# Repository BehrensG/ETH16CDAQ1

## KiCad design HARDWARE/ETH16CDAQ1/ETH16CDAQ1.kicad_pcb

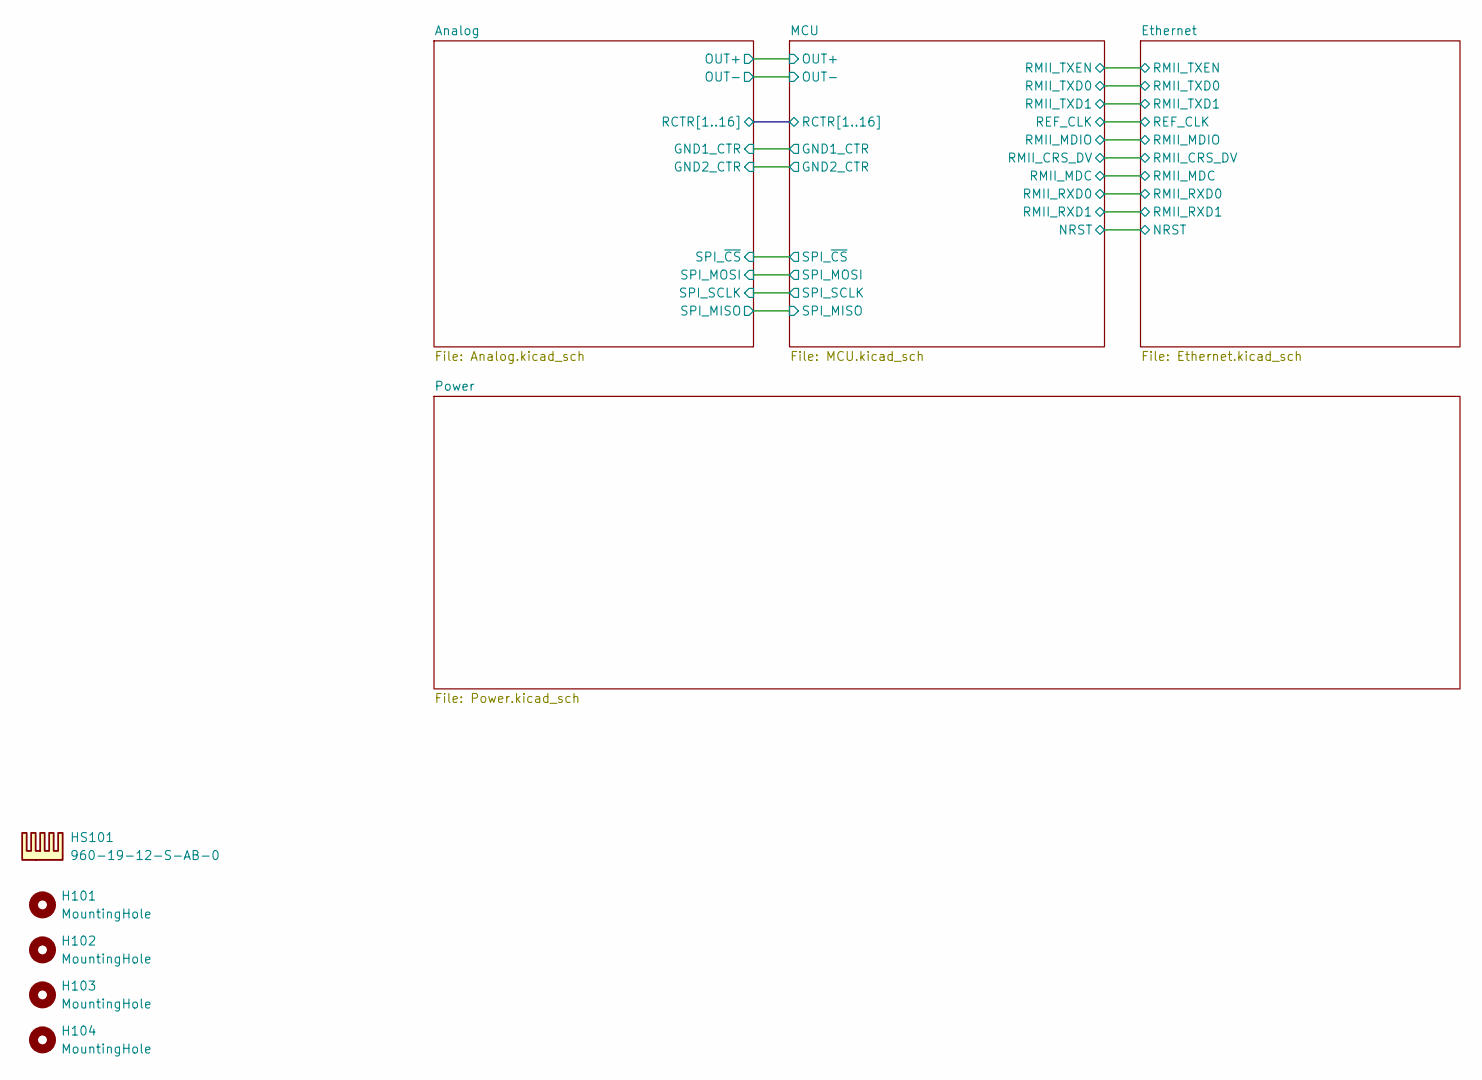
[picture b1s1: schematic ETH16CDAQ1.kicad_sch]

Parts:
H101, H102: MountingHole; MountingHole_3.2mm_M3_DIN965_Pad
H103, H104: MountingHole; MountingHole_2.2mm_M2_DIN965
HS101: 960-19-12-S-AB-0

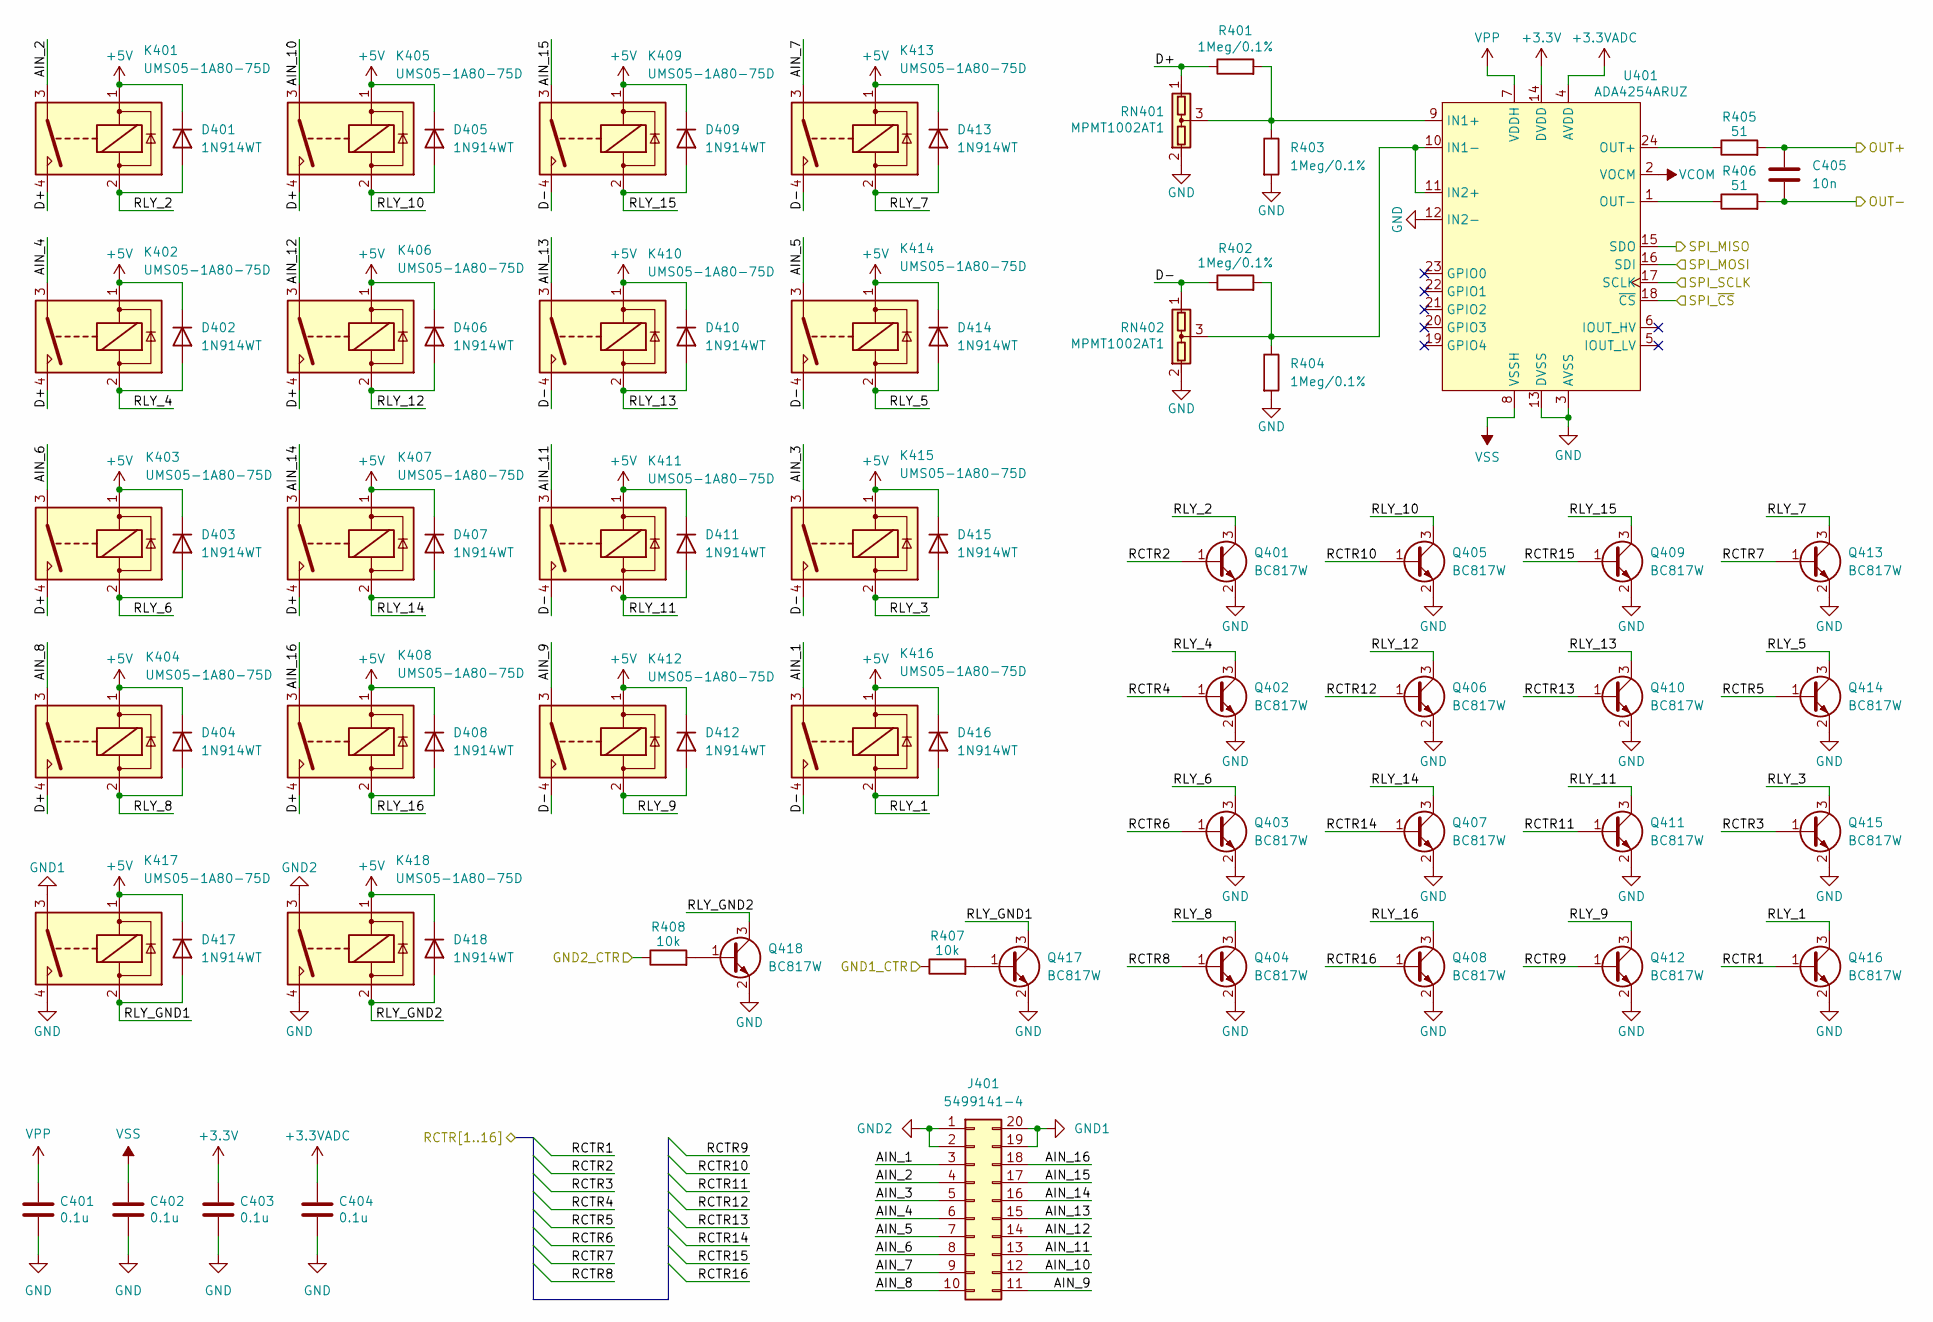
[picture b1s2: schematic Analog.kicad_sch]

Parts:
C401, C402, C403, C404: 0.1u; C_0603_1608Metric_Pad1.08x0.95mm_HandSolder
C405: 10n; C_0603_1608Metric_Pad1.08x0.95mm_HandSolder
D401, D402, D403, D404, D405, D406, D407, D408, D409, D410, D411, D412, D413, D414, D415, D416, D417, D418: 1N914WT; D_SOD-523
J401: 5499141-4; IDC-Header_2x10-1MP_P2.54mm_Latch_Horizontal
K401, K402, K403, K404, K405, K406, K407, K408, K409, K410, K411, K412, K413, K414, K415, K416, K417, K418: UMS05-1A80-75D; Relay_StandexMeder_UMS
Q401, Q402, Q403, Q404, Q405, Q406, Q407, Q408, Q409, Q410, Q411, Q412, Q413, Q414, Q415, Q416, Q417, Q418: BC817W; SOT-323_SC-70
R401, R402, R403, R404: 1Meg/0.1%; R_0805_2012Metric_Pad1.20x1.40mm_HandSolder
R405, R406: 51; R_0603_1608Metric_Pad0.98x0.95mm_HandSolder
R407, R408: 10k; R_0603_1608Metric_Pad0.98x0.95mm_HandSolder
RN401, RN402: MPMT1002AT1; SOT-23
U401: ADA4254ARUZ; TSSOP-24_4.4x7.8mm_P0.65mm

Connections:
+3.3V: C403.1, U401.14 (DVDD); also elsewhere on the board
+3.3VADC: C404.1, U401.4 (AVDD); also elsewhere on the board
+5V: D401.1 (K), D402.1 (K), D403.1 (K), D404.1 (K), D405.1 (K), D406.1 (K), D407.1 (K), D408.1 (K), D409.1 (K), D410.1 (K), D411.1 (K), D412.1 (K), D413.1 (K), D414.1 (K), D415.1 (K), D416.1 (K), D417.1 (K), D418.1 (K), K401.1, K402.1, K403.1, K404.1, K405.1, K406.1, K407.1, K408.1, K409.1, K410.1, K411.1, K412.1, K413.1, K414.1, K415.1, K416.1, K417.1, K418.1; also elsewhere on the board
/Analog/AIN_1: J401.3, K416.3
/Analog/AIN_2: J401.4, K401.3
/Analog/AIN_3: J401.5, K415.3
/Analog/AIN_4: J401.6, K402.3
/Analog/AIN_5: J401.7, K414.3
/Analog/AIN_6: J401.8, K403.3
/Analog/AIN_7: J401.9, K413.3
/Analog/AIN_8: J401.10, K404.3
/Analog/AIN_9: J401.11, K412.3
/Analog/AIN_10: J401.12, K405.3
/Analog/AIN_11: J401.13, K411.3
/Analog/AIN_12: J401.14, K406.3
/Analog/AIN_13: J401.15, K410.3
/Analog/AIN_14: J401.16, K407.3
/Analog/AIN_15: J401.17, K409.3
/Analog/AIN_16: J401.18, K408.3
/Analog/D+: K401.4, K402.4, K403.4, K404.4, K405.4, K406.4, K407.4, K408.4, R401.1, RN401.1
/Analog/D-: K409.4, K410.4, K411.4, K412.4, K413.4, K414.4, K415.4, K416.4, R402.1, RN402.1
/Analog/GND1_CTR: R407.1; also elsewhere on the board
/Analog/GND2_CTR: R408.1; also elsewhere on the board
/Analog/OUT+: C405.1, R405.2; also elsewhere on the board
/Analog/OUT-: C405.2, R406.2; also elsewhere on the board
/Analog/RCTR1: Q416.1 (B); also elsewhere on the board
/Analog/RCTR2: Q401.1 (B); also elsewhere on the board
/Analog/RCTR3: Q415.1 (B); also elsewhere on the board
/Analog/RCTR4: Q402.1 (B); also elsewhere on the board
/Analog/RCTR5: Q414.1 (B); also elsewhere on the board
/Analog/RCTR6: Q403.1 (B); also elsewhere on the board
/Analog/RCTR7: Q413.1 (B); also elsewhere on the board
/Analog/RCTR8: Q404.1 (B); also elsewhere on the board
/Analog/RCTR9: Q412.1 (B); also elsewhere on the board
/Analog/RCTR10: Q405.1 (B); also elsewhere on the board
/Analog/RCTR11: Q411.1 (B); also elsewhere on the board
/Analog/RCTR12: Q406.1 (B); also elsewhere on the board
/Analog/RCTR13: Q410.1 (B); also elsewhere on the board
/Analog/RCTR14: Q407.1 (B); also elsewhere on the board
/Analog/RCTR15: Q409.1 (B); also elsewhere on the board
/Analog/RCTR16: Q408.1 (B); also elsewhere on the board
/Analog/RLY_1: D416.2 (A), K416.2, Q416.3 (C)
/Analog/RLY_2: D401.2 (A), K401.2, Q401.3 (C)
/Analog/RLY_3: D415.2 (A), K415.2, Q415.3 (C)
/Analog/RLY_4: D402.2 (A), K402.2, Q402.3 (C)
/Analog/RLY_5: D414.2 (A), K414.2, Q414.3 (C)
/Analog/RLY_6: D403.2 (A), K403.2, Q403.3 (C)
/Analog/RLY_7: D413.2 (A), K413.2, Q413.3 (C)
/Analog/RLY_8: D404.2 (A), K404.2, Q404.3 (C)
/Analog/RLY_9: D412.2 (A), K412.2, Q412.3 (C)
/Analog/RLY_10: D405.2 (A), K405.2, Q405.3 (C)
/Analog/RLY_11: D411.2 (A), K411.2, Q411.3 (C)
/Analog/RLY_12: D406.2 (A), K406.2, Q406.3 (C)
/Analog/RLY_13: D410.2 (A), K410.2, Q410.3 (C)
/Analog/RLY_14: D407.2 (A), K407.2, Q407.3 (C)
/Analog/RLY_15: D409.2 (A), K409.2, Q409.3 (C)
/Analog/RLY_16: D408.2 (A), K408.2, Q408.3 (C)
/Analog/RLY_GND1: D417.2 (A), K417.2, Q417.3 (C)
/Analog/RLY_GND2: D418.2 (A), K418.2, Q418.3 (C)
/Analog/SPI_MISO: U401.15 (SDO); also elsewhere on the board
/Analog/SPI_MOSI: U401.16 (SDI); also elsewhere on the board
/Analog/SPI_SCLK: U401.17 (SCLK); also elsewhere on the board
/Analog/SPI_~CS: U401.18 (~CS); also elsewhere on the board
GND: C401.2, C402.2, C403.2, C404.2, K417.4, K418.4, Q401.2 (E), Q402.2 (E), Q403.2 (E), Q404.2 (E), Q405.2 (E), Q406.2 (E), Q407.2 (E), Q408.2 (E), Q409.2 (E), Q410.2 (E), Q411.2 (E), Q412.2 (E), Q413.2 (E), Q414.2 (E), Q415.2 (E), Q416.2 (E), Q417.2 (E), Q418.2 (E), R403.2, R404.2, RN401.2, RN402.2, U401.3 (AVSS), U401.12 (IN2-), U401.13 (DVSS); also elsewhere on the board
GND1: J401.19, J401.20, K417.3
GND2: J401.1, J401.2, K418.3
unnamed: Q417.1 (B), R407.2
unnamed: Q418.1 (B), R408.2
unnamed: R401.2, R403.1, RN401.3, U401.9 (IN1+)
unnamed: R402.2, R404.1, RN402.3, U401.10 (IN1-), U401.11 (IN2+)
unnamed: R405.1, U401.24 (OUT+)
unnamed: R406.1, U401.1 (OUT-)
VCOM: U401.2 (VOCM); also elsewhere on the board
VPP: C401.1, U401.7 (VDDH); also elsewhere on the board
VSS: C402.1, U401.8 (VSSH); also elsewhere on the board

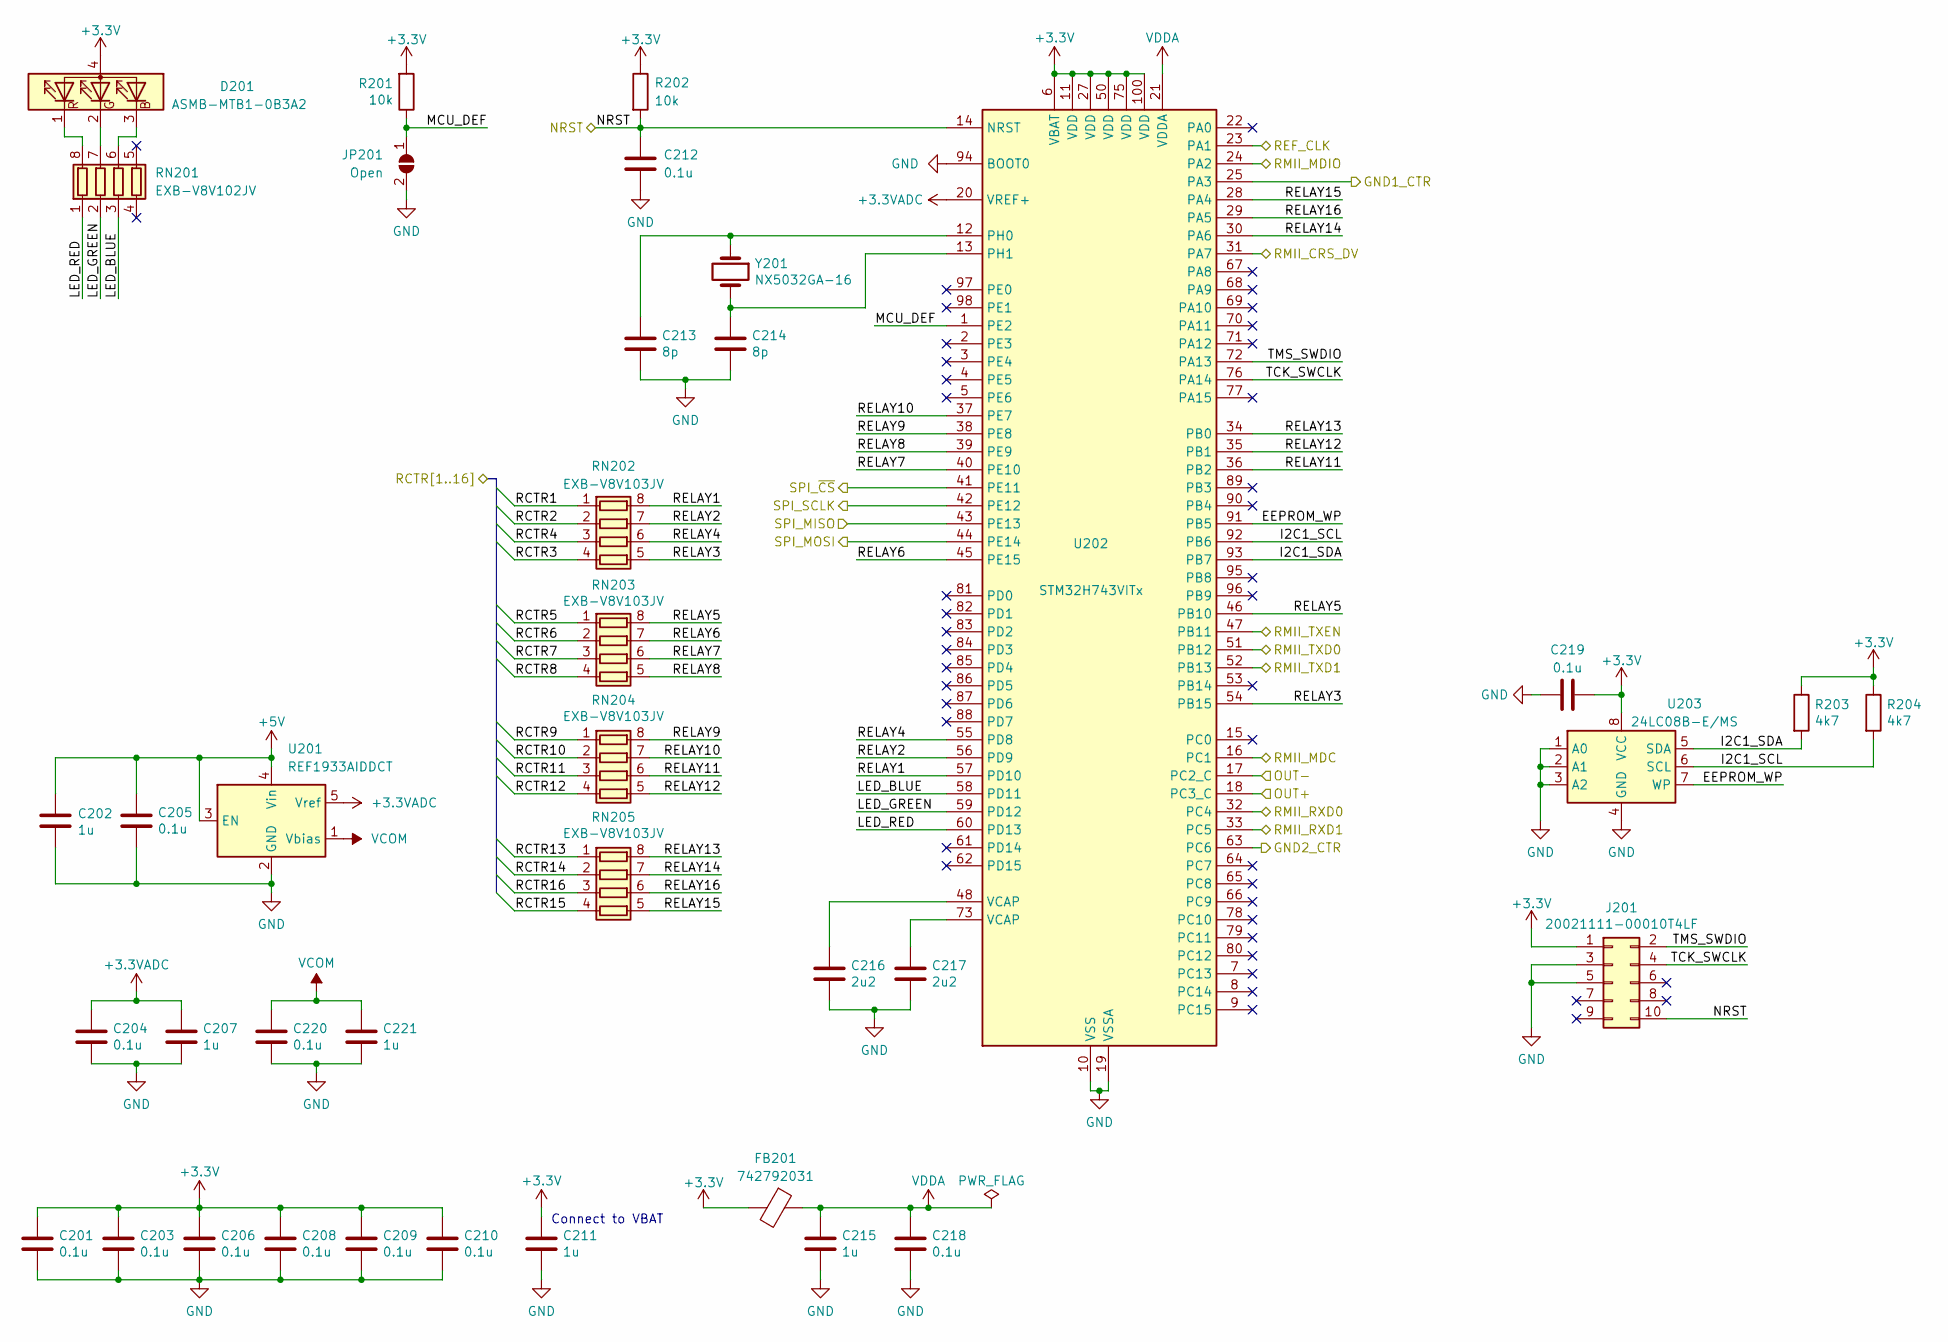
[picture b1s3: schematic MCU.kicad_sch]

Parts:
C201, C203, C204, C205, C206, C208, C209, C210, C212, C218, C219, C220: 0.1u; C_0603_1608Metric_Pad1.08x0.95mm_HandSolder
C202, C207, C211, C215, C221: 1u; C_0603_1608Metric_Pad1.08x0.95mm_HandSolder
C213, C214: 8p; C_0603_1608Metric_Pad1.08x0.95mm_HandSolder
C216, C217: 2u2; C_0603_1608Metric_Pad1.08x0.95mm_HandSolder
D201: ASMB-MTB1-0B3A2; LED_Avago_PLCC4_3.2x2.8mm_CW
FB201: 742792031; L_0805_2012Metric_Pad1.05x1.20mm_HandSolder
J201: 20021111-00010T4LF; PinHeader_2x05_P1.27mm_Vertical
JP201: Open; SolderJumper-2_P1.3mm_Open_Pad1.0x1.5mm
R201, R202: 10k; R_0603_1608Metric_Pad0.98x0.95mm_HandSolder
R203, R204: 4k7; R_0603_1608Metric_Pad0.98x0.95mm_HandSolder
RN201: EXB-V8V102JV; R_Array_Concave_4x0603
RN202, RN203, RN204, RN205: EXB-V8V103JV; R_Array_Concave_4x0603
U201: REF1933AIDDCT; TSOT-23-5
U202: STM32H743VITx; LQFP-100_14x14mm_P0.5mm
U203: 24LC08B-E/MS; MSOP-8_3x3mm_P0.65mm
Y201: NX5032GA-16; NX5032GA

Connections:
+3.3V: C201.1, C203.1, C206.1, C208.1, C209.1, C210.1, C211.1, C219.2, D201.4 (A), FB201.2, J201.1, R201.2, R202.1, R203.1, R204.1, U202.6 (VBAT), U202.11 (VDD), U202.27 (VDD), U202.50 (VDD), U202.75 (VDD), U202.100 (VDD), U203.8 (VCC); also elsewhere on the board
+3.3VADC: C204.1, C207.1, U201.5 (Vref), U202.20 (VREF+); also elsewhere on the board
+5V: C202.1, C205.1, U201.3 (EN), U201.4 (Vin); also elsewhere on the board
/Analog/GND1_CTR: U202.25 (PA3); also elsewhere on the board
/Analog/GND2_CTR: U202.63 (PC6); also elsewhere on the board
/Analog/OUT+: U202.18 (PC3_C); also elsewhere on the board
/Analog/OUT-: U202.17 (PC2_C); also elsewhere on the board
/Analog/RCTR1: RN202.1 (R1.1); also elsewhere on the board
/Analog/RCTR2: RN202.2 (R2.1); also elsewhere on the board
/Analog/RCTR3: RN202.4 (R4.1); also elsewhere on the board
/Analog/RCTR4: RN202.3 (R3.1); also elsewhere on the board
/Analog/RCTR5: RN203.1 (R1.1); also elsewhere on the board
/Analog/RCTR6: RN203.2 (R2.1); also elsewhere on the board
/Analog/RCTR7: RN203.3 (R3.1); also elsewhere on the board
/Analog/RCTR8: RN203.4 (R4.1); also elsewhere on the board
/Analog/RCTR9: RN204.1 (R1.1); also elsewhere on the board
/Analog/RCTR10: RN204.2 (R2.1); also elsewhere on the board
/Analog/RCTR11: RN204.3 (R3.1); also elsewhere on the board
/Analog/RCTR12: RN204.4 (R4.1); also elsewhere on the board
/Analog/RCTR13: RN205.1 (R1.1); also elsewhere on the board
/Analog/RCTR14: RN205.2 (R2.1); also elsewhere on the board
/Analog/RCTR15: RN205.4 (R4.1); also elsewhere on the board
/Analog/RCTR16: RN205.3 (R3.1); also elsewhere on the board
/Analog/SPI_MISO: U202.43 (PE13); also elsewhere on the board
/Analog/SPI_MOSI: U202.44 (PE14); also elsewhere on the board
/Analog/SPI_SCLK: U202.42 (PE12); also elsewhere on the board
/Analog/SPI_~CS: U202.41 (PE11); also elsewhere on the board
/Ethernet/REF_CLK: U202.23 (PA1); also elsewhere on the board
/Ethernet/RMII_CRS_DV: U202.31 (PA7); also elsewhere on the board
/Ethernet/RMII_MDC: U202.16 (PC1); also elsewhere on the board
/Ethernet/RMII_MDIO: U202.24 (PA2); also elsewhere on the board
/Ethernet/RMII_RXD0: U202.32 (PC4); also elsewhere on the board
/Ethernet/RMII_RXD1: U202.33 (PC5); also elsewhere on the board
/Ethernet/RMII_TXD0: U202.51 (PB12); also elsewhere on the board
/Ethernet/RMII_TXD1: U202.52 (PB13); also elsewhere on the board
/Ethernet/RMII_TXEN: U202.47 (PB11); also elsewhere on the board
/MCU/EEPROM_WP: U202.91 (PB5), U203.7 (WP)
/MCU/I2C1_SCL: R204.2, U202.92 (PB6), U203.6 (SCL)
/MCU/I2C1_SDA: R203.2, U202.93 (PB7), U203.5 (SDA)
/MCU/LED_BLUE: RN201.3 (R3.1), U202.58 (PD11)
/MCU/LED_GREEN: RN201.2 (R2.1), U202.59 (PD12)
/MCU/LED_RED: RN201.1 (R1.1), U202.60 (PD13)
/MCU/MCU_DEF: JP201.1 (A), R201.1, U202.1 (PE2)
/MCU/NRST: C212.1, J201.10, R202.2, U202.14 (NRST); also elsewhere on the board
/MCU/RELAY1: RN202.8 (R1.2), U202.57 (PD10)
/MCU/RELAY2: RN202.7 (R2.2), U202.56 (PD9)
/MCU/RELAY3: RN202.5 (R4.2), U202.54 (PB15)
/MCU/RELAY4: RN202.6 (R3.2), U202.55 (PD8)
/MCU/RELAY5: RN203.8 (R1.2), U202.46 (PB10)
/MCU/RELAY6: RN203.7 (R2.2), U202.45 (PE15)
/MCU/RELAY7: RN203.6 (R3.2), U202.40 (PE10)
/MCU/RELAY8: RN203.5 (R4.2), U202.39 (PE9)
/MCU/RELAY9: RN204.8 (R1.2), U202.38 (PE8)
/MCU/RELAY10: RN204.7 (R2.2), U202.37 (PE7)
/MCU/RELAY11: RN204.6 (R3.2), U202.36 (PB2)
/MCU/RELAY12: RN204.5 (R4.2), U202.35 (PB1)
/MCU/RELAY13: RN205.8 (R1.2), U202.34 (PB0)
/MCU/RELAY14: RN205.7 (R2.2), U202.30 (PA6)
/MCU/RELAY15: RN205.5 (R4.2), U202.28 (PA4)
/MCU/RELAY16: RN205.6 (R3.2), U202.29 (PA5)
/MCU/TCK_SWCLK: J201.4, U202.76 (PA14)
/MCU/TMS_SWDIO: J201.2, U202.72 (PA13)
GND: C201.2, C202.2, C203.2, C204.2, C205.2, C206.2, C207.2, C208.2, C209.2, C210.2, C211.2, C212.2, C213.2, C214.2, C215.2, C216.2, C217.2, C218.2, C219.1, C220.2, C221.2, J201.3, J201.5, JP201.2 (B), U201.2 (GND), U202.10 (VSS), U202.19 (VSSA), U202.26 (VSS), U202.49 (VSS), U202.74 (VSS), U202.94 (BOOT0), U202.99 (VSS), U203.1 (A0), U203.2 (A1), U203.3 (A2), U203.4 (GND); also elsewhere on the board
unnamed: C216.1, U202.48 (VCAP)
unnamed: C217.1, U202.73 (VCAP)
unnamed: D201.3 (BK), RN201.6 (R3.2)
unnamed: D201.2 (GK), RN201.7 (R2.2)
unnamed: D201.1 (RK), RN201.8 (R1.2)
unnamed: C213.1, U202.12 (PH0), Y201.1
unnamed: C214.1, U202.13 (PH1), Y201.2
VCOM: C220.1, C221.1, U201.1 (Vbias); also elsewhere on the board
VDDA: C215.1, C218.1, FB201.1, U202.21 (VDDA)

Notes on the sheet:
Connect to VBAT

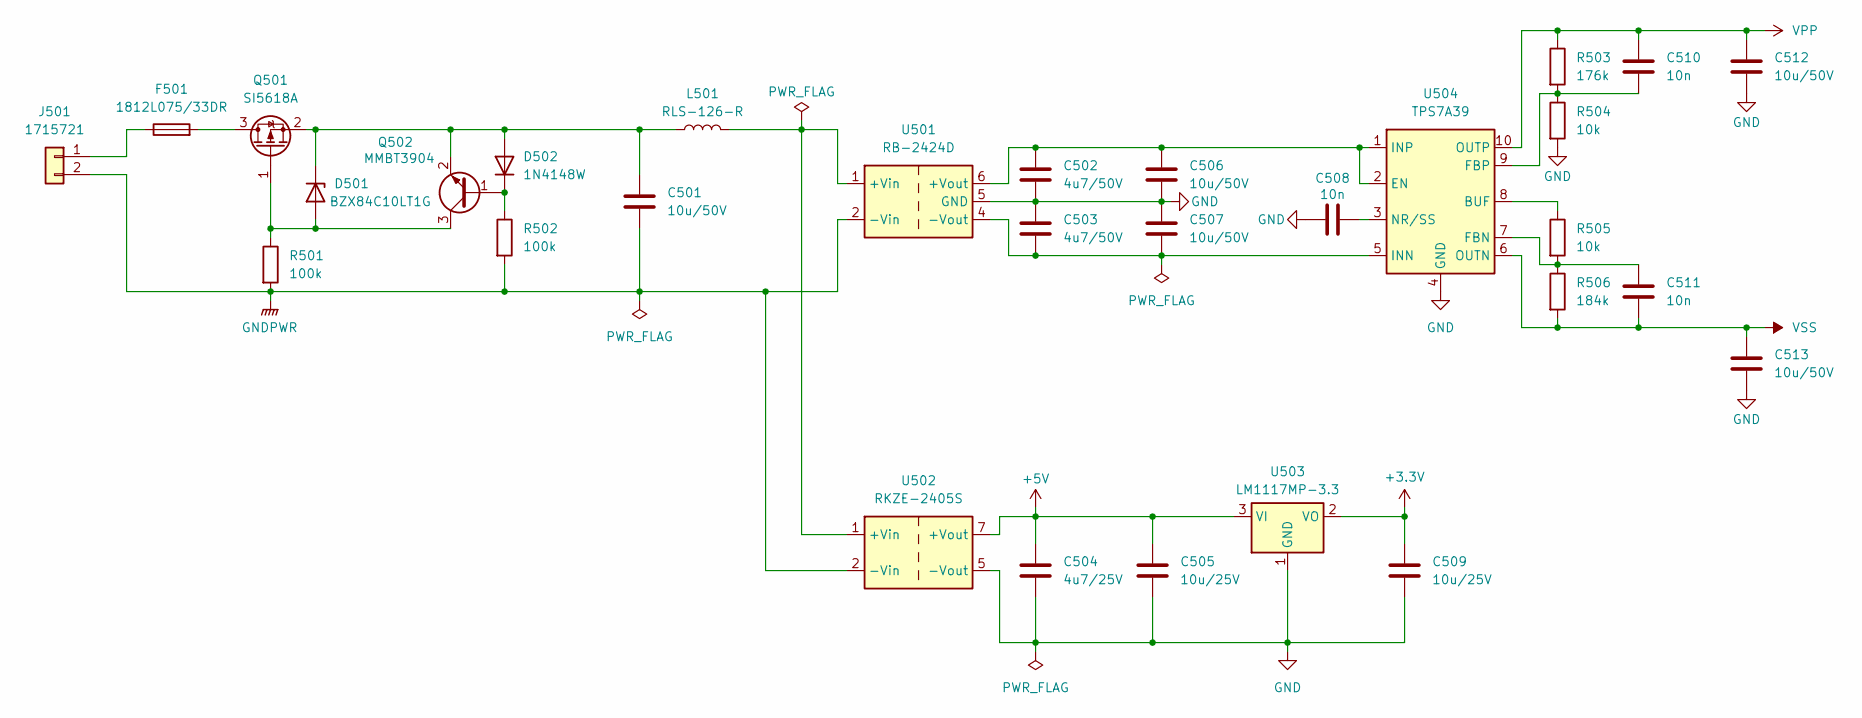
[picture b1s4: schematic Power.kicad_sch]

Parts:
C501, C506, C507, C512, C513: 10u/50V; C_1206_3216Metric_Pad1.33x1.80mm_HandSolder
C502, C503: 4u7/50V; C_1206_3216Metric_Pad1.33x1.80mm_HandSolder
C504: 4u7/25V; C_1206_3216Metric_Pad1.33x1.80mm_HandSolder
C505, C509: 10u/25V; C_1206_3216Metric_Pad1.33x1.80mm_HandSolder
C508, C510, C511: 10n; C_0603_1608Metric_Pad1.08x0.95mm_HandSolder
D501: BZX84C10LT1G; SOT-23
D502: 1N4148W; D_SOD-123
F501: 1812L075/33DR; Fuse_1812_4532Metric_Pad1.30x3.40mm_HandSolder
J501: 1715721; TerminalBlock_Phoenix_MKDS-1,5-2_1x02_P5.00mm_Horizontal
L501: RLS-126-R; IND_RLS-126-R
Q501: SI5618A; SOT-23
Q502: MMBT3904; SOT-23
R501, R502: 100k; R_0603_1608Metric_Pad0.98x0.95mm_HandSolder
R503: 176k; R_0603_1608Metric_Pad0.98x0.95mm_HandSolder
R504, R505: 10k; R_0603_1608Metric_Pad0.98x0.95mm_HandSolder
R506: 184k; R_0603_1608Metric_Pad0.98x0.95mm_HandSolder
U501: RB-2424D; CONV_RB-2424D
U502: RKZE-2405S; CONV_RKZE-2405S
U503: LM1117MP-3.3; SOT-223-3_TabPin2
U504: TPS7A39; Texas_S-PVSON-N10_ThermalVias

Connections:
+3.3V: C509.1, U503.2 (VO); also elsewhere on the board
+5V: C504.1, C505.1, U502.7 (+Vout), U503.3 (VI); also elsewhere on the board
GND: C502.2, C503.1, C504.2, C505.2, C506.2, C507.1, C508.1, C509.2, C512.2, C513.2, R504.2, U501.5 (GND), U502.5 (-Vout), U503.1 (GND), U504.4 (GND), U504.11 (GND); also elsewhere on the board
GNDPWR: C501.2, J501.2, R501.2, R502.2, U501.2 (-Vin), U502.2 (-Vin)
unnamed: D501.1 (A), Q501.1 (G), Q502.3 (C), R501.1
unnamed: C501.1, D501.3 (K), D502.2 (A), L501.1, Q501.2 (S), Q502.2 (E)
unnamed: D502.1 (K), Q502.1 (B), R502.1
unnamed: F501.1, J501.1
unnamed: F501.2, Q501.3 (D)
unnamed: L501.2, U501.1 (+Vin), U502.1 (+Vin)
unnamed: C502.1, C506.1, U501.6 (+Vout), U504.1 (INP), U504.2 (EN)
unnamed: C503.2, C507.2, U501.4 (-Vout), U504.5 (INN)
unnamed: R505.1, U504.8 (BUF)
unnamed: C511.1, R505.2, R506.1, U504.7 (FBN)
unnamed: C510.2, R503.2, R504.1, U504.9 (FBP)
unnamed: C508.2, U504.3 (NR/SS)
VPP: C510.1, C512.1, R503.1, U504.10 (OUTP); also elsewhere on the board
VSS: C511.2, C513.1, R506.2, U504.6 (OUTN); also elsewhere on the board

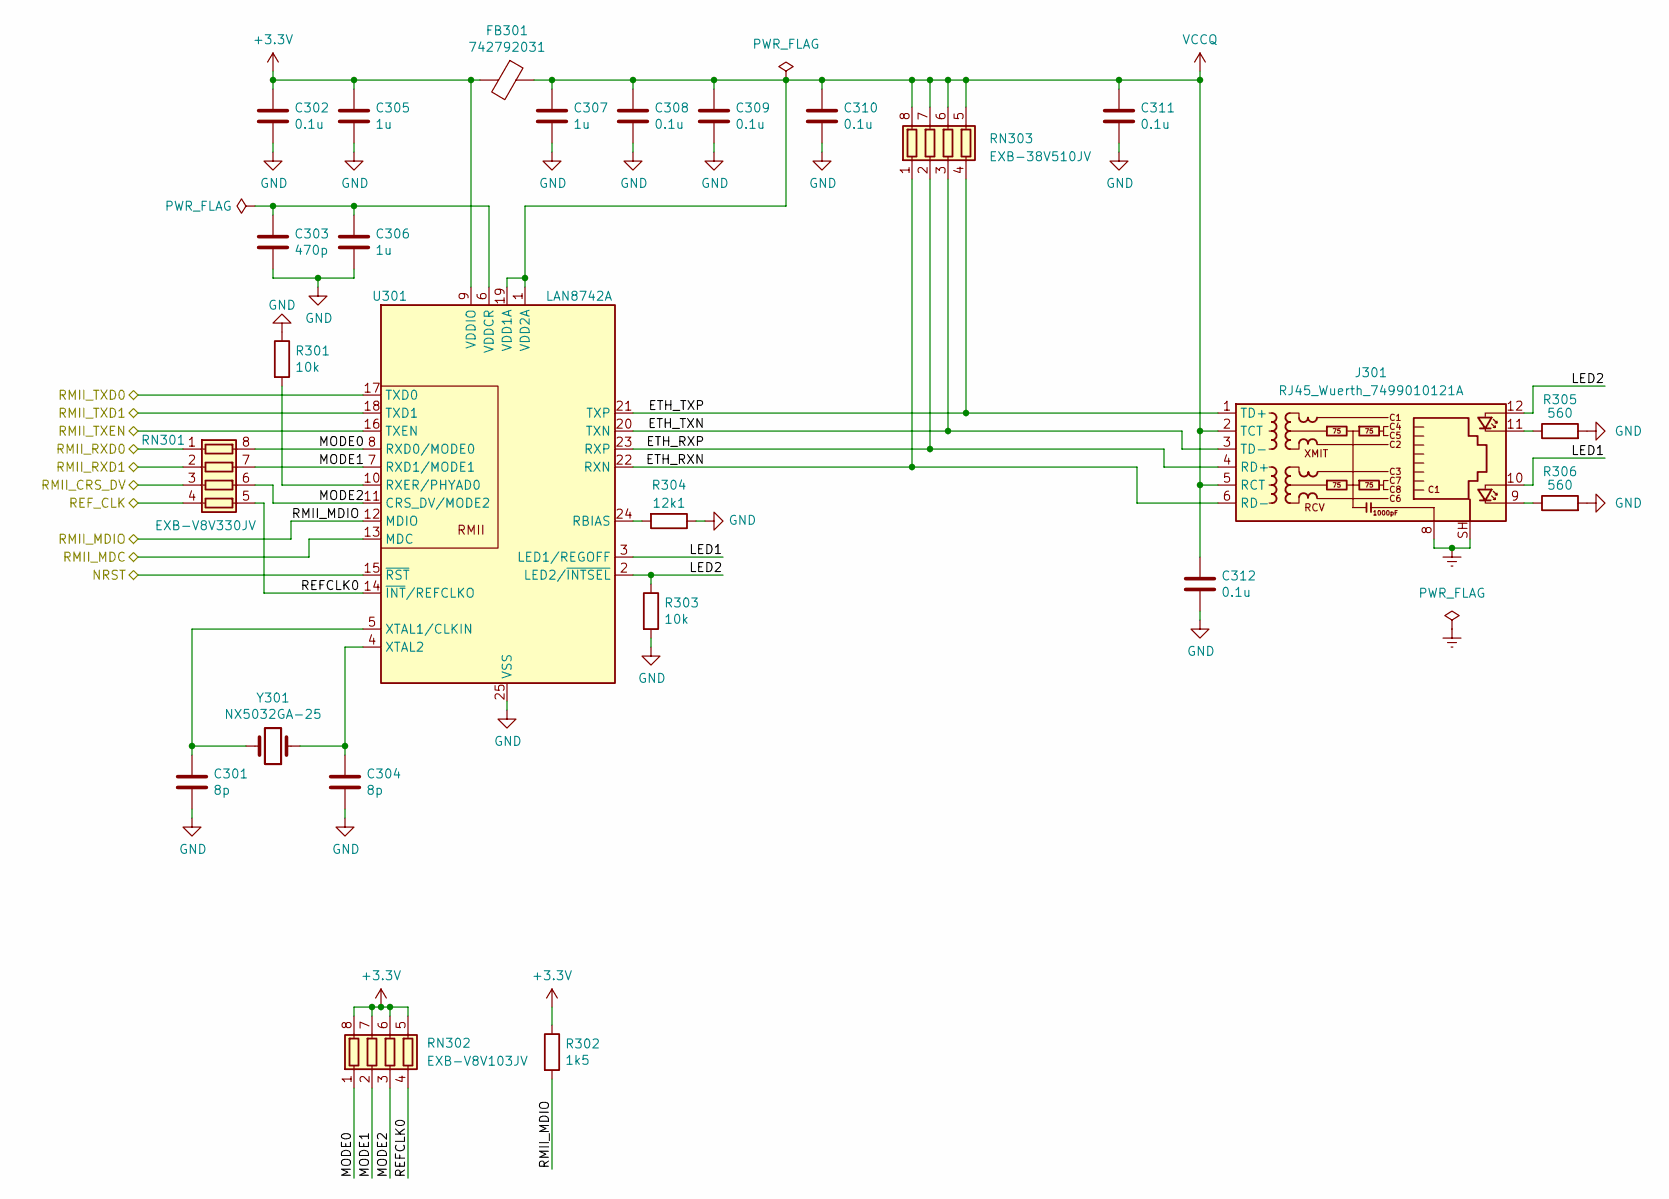
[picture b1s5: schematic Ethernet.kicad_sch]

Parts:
C301, C304: 8p; C_0603_1608Metric_Pad1.08x0.95mm_HandSolder
C302, C308, C309, C310, C311, C312: 0.1u; C_0603_1608Metric_Pad1.08x0.95mm_HandSolder
C303: 470p; C_0603_1608Metric_Pad1.08x0.95mm_HandSolder
C305, C306, C307: 1u; C_0603_1608Metric_Pad1.08x0.95mm_HandSolder
FB301: 742792031; L_0805_2012Metric_Pad1.05x1.20mm_HandSolder
J301: RJ45_Wuerth_7499010121A; RJ45_Wuerth_7499010121A_Horizontal
R301, R303: 10k; R_0603_1608Metric_Pad0.98x0.95mm_HandSolder
R302: 1k5; R_0603_1608Metric_Pad0.98x0.95mm_HandSolder
R304: 12k1; R_0603_1608Metric_Pad0.98x0.95mm_HandSolder
R305, R306: 560; R_0603_1608Metric_Pad0.98x0.95mm_HandSolder
RN301: EXB-V8V330JV; R_Array_Concave_4x0603
RN302: EXB-V8V103JV; R_Array_Concave_4x0603
RN303: EXB-38V510JV; R_Array_Concave_4x0603
U301: LAN8742A; VQFN-24-1EP_4x4mm_P0.5mm_EP2.5x2.5mm_ThermalVias
Y301: NX5032GA-25; NX5032GA

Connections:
+3.3V: C302.1, C305.1, FB301.2, R302.1, RN302.5 (R4.2), RN302.6 (R3.2), RN302.7 (R2.2), RN302.8 (R1.2), U301.9 (VDDIO); also elsewhere on the board
/Ethernet/ETH_RXN: J301.6 (RD-), RN303.1 (R1.1), U301.22 (RXN)
/Ethernet/ETH_RXP: J301.4 (RD+), RN303.2 (R2.1), U301.23 (RXP)
/Ethernet/ETH_TXN: J301.3 (TD-), RN303.3 (R3.1), U301.20 (TXN)
/Ethernet/ETH_TXP: J301.1 (TD+), RN303.4 (R4.1), U301.21 (TXP)
/Ethernet/LED1: J301.10, U301.3 (LED1/REGOFF)
/Ethernet/LED2: J301.12, R303.1, U301.2 (LED2/~INTSEL)
/Ethernet/MODE0: RN301.8 (R1.2), RN302.1 (R1.1), U301.8 (RXD0/MODE0)
/Ethernet/MODE1: RN301.7 (R2.2), RN302.2 (R2.1), U301.7 (RXD1/MODE1)
/Ethernet/MODE2: RN301.6 (R3.2), RN302.3 (R3.1), U301.11 (CRS_DV/MODE2)
/Ethernet/REFCLK0: RN301.5 (R4.2), RN302.4 (R4.1), U301.14 (~INT/REFCLKO)
/Ethernet/REF_CLK: RN301.4 (R4.1); also elsewhere on the board
/Ethernet/RMII_CRS_DV: RN301.3 (R3.1); also elsewhere on the board
/Ethernet/RMII_MDC: U301.13 (MDC); also elsewhere on the board
/Ethernet/RMII_MDIO: R302.2, U301.12 (MDIO); also elsewhere on the board
/Ethernet/RMII_RXD0: RN301.1 (R1.1); also elsewhere on the board
/Ethernet/RMII_RXD1: RN301.2 (R2.1); also elsewhere on the board
/Ethernet/RMII_TXD0: U301.17 (TXD0); also elsewhere on the board
/Ethernet/RMII_TXD1: U301.18 (TXD1); also elsewhere on the board
/Ethernet/RMII_TXEN: U301.16 (TXEN); also elsewhere on the board
/MCU/NRST: U301.15 (~RST); also elsewhere on the board
Earth: J301.8, J301.SH
GND: C301.2, C302.2, C303.2, C304.2, C305.2, C306.2, C307.2, C308.2, C309.2, C310.2, C311.2, C312.2, R301.1, R303.2, R304.1, R305.2, R306.2, U301.25 (VSS); also elsewhere on the board
unnamed: J301.9, R306.1
unnamed: J301.11, R305.1
unnamed: R304.2, U301.24 (RBIAS)
unnamed: R301.2, U301.10 (RXER/PHYAD0)
unnamed: C303.1, C306.1, U301.6 (VDDCR)
unnamed: C301.1, U301.5 (XTAL1/CLKIN), Y301.2
unnamed: C304.1, U301.4 (XTAL2), Y301.1
VCCQ: C307.1, C308.1, C309.1, C310.1, C311.1, C312.1, FB301.1, J301.2 (TCT), J301.5 (RCT), RN303.5 (R4.2), RN303.6 (R3.2), RN303.7 (R2.2), RN303.8 (R1.2), U301.1 (VDD2A), U301.19 (VDD1A)

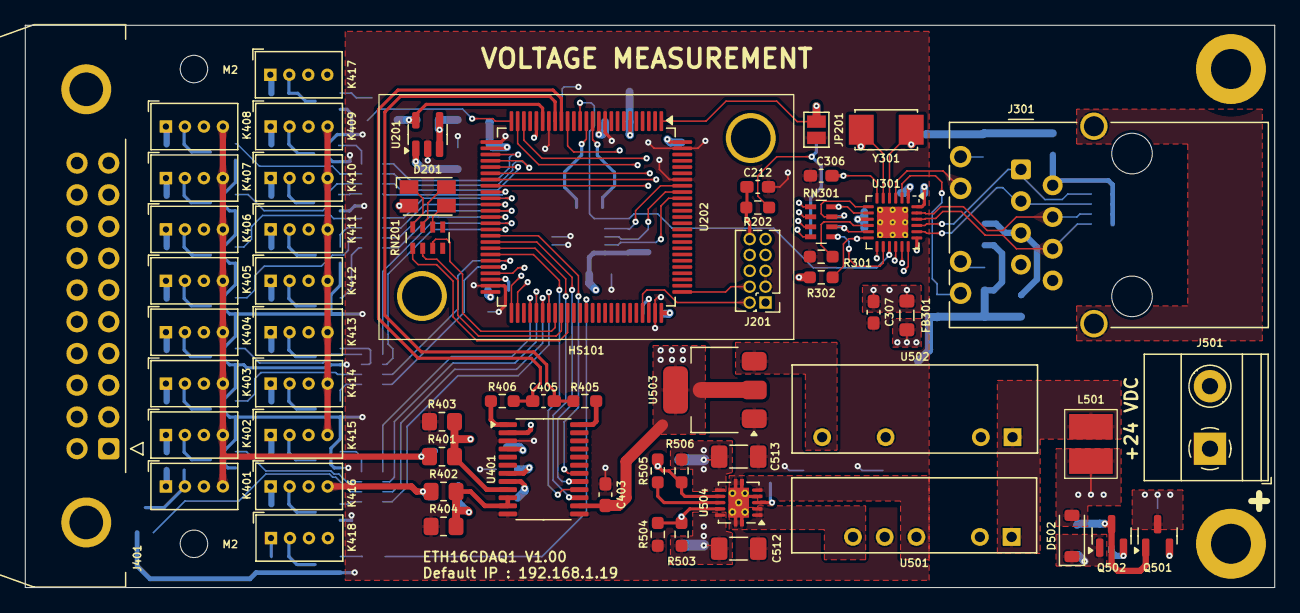
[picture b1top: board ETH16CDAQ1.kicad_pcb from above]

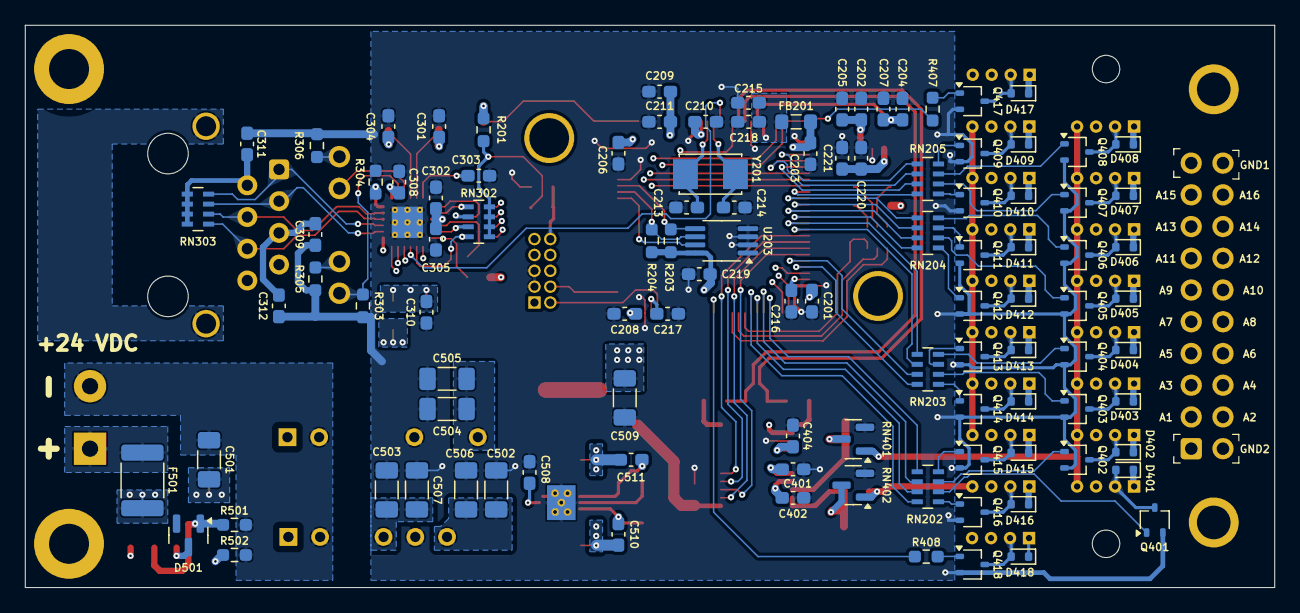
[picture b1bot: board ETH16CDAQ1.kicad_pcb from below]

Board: 4 copper layers, 100.0 x 45.0 mm, 169 parts (104 on the bottom side), 150 nets.

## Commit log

2024-04-11 Development
